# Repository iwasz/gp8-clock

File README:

Stopwatch project for moto-gymkhana.
In case you don't know what is moto-gymkhana : https://www.youtube.com/watch?v=KFEh59GVMnQ

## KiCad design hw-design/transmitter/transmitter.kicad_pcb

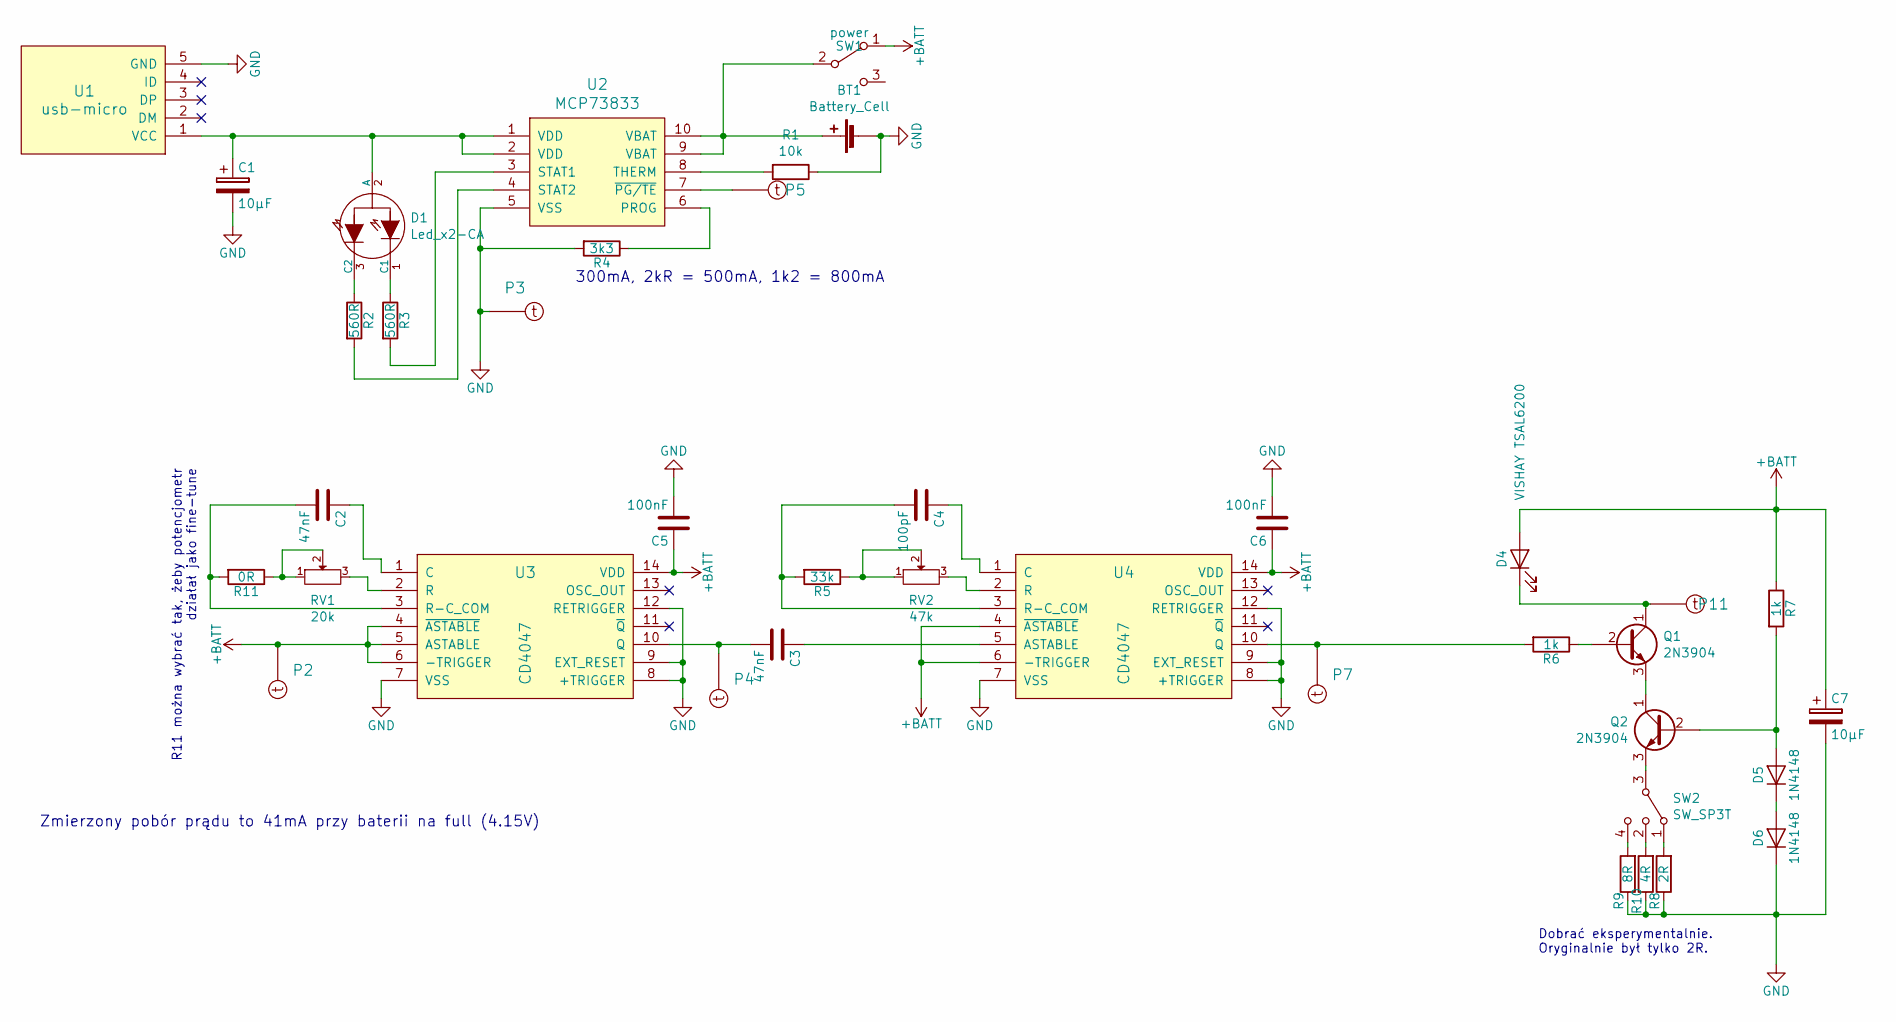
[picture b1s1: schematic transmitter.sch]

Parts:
BT1: Battery_Cell; BatteryHolder_MPD_BH-18650-PC2
C1, C7: 10µF; c_tant_B-pins21
C2, C3: 47nF; C_0603_1608Metric
C4: 100pF; C_0603_1608Metric
C5, C6: 100nF; C_0603_1608Metric
D1: Led_x2-CA; led_3mm-3pins
D4: VISHAY TSAL6200; LED_D5.0mm_Horizontal_O3.81mm_Z3.0mm
D5, D6: 1N4148; D_SOD-323
P2, P3, P4, P5, P7, P11: test-double; testpad-2p
Q1, Q2: 2N3904; TO-92
R1: 10k; R_0603_1608Metric
R2, R3: 560R; R_0603_1608Metric
R4: 3k3; R_0603_1608Metric
R5: 33k; R_0603_1608Metric
R6, R7: 1k; R_0603_1608Metric
R8: 2R; R_0805_2012Metric
R9: 8R; R_0805_2012Metric
R10: 4R; R_0805_2012Metric
R11: 0R; R_0603_1608Metric
RV1: 20k; Potentiometer_Bourns_3296W_Vertical
RV2: 47k; Potentiometer_Bourns_3296W_Vertical
SW1: power; MFP 201 NR
SW2: SW_SP3T; MFP-1323-R
U1: usb-micro; conn_usb_B_micro_smd-2-nohole
U2: MCP73833; MSOP-10_3x3mm_P0.5mm
U3, U4: CD4047; SOIC-14_3.9x8.7mm_P1.27mm

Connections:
+BATT: C5.1, C6.1, C7.1, D4.2 (A), P2.1, R7.1, SW1.1 (A), U3.4 (~ASTABLE), U3.5 (ASTABLE), U3.6 (-TRIGGER), U3.14 (VDD), U4.4 (~ASTABLE), U4.6 (-TRIGGER), U4.14 (VDD)
GND: BT1.2 (-), C1.2, C5.2, C6.2, C7.2, D6.1 (K), P3.1, R1.1, R4.2, R8.1, R9.1, R10.1, U1.5 (GND), U2.5 (VSS), U3.7 (VSS), U3.8 (+TRIGGER), U3.9 (EXT_RESET), U3.12 (RETRIGGER), U4.7 (VSS), U4.8 (+TRIGGER), U4.9 (EXT_RESET), U4.12 (RETRIGGER)
unnamed: BT1.1 (+), SW1.2 (B), U2.9 (VBAT), U2.10 (VBAT)
unnamed: C1.1, D1.2 (A), U1.1 (VCC), U2.1 (VDD), U2.2 (VDD)
unnamed: C2.1, U3.1 (C)
unnamed: C2.2, R11.2, U3.3 (R-C_COM)
unnamed: C3.1, U4.5 (ASTABLE)
unnamed: C3.2, P4.1, U3.10 (Q)
unnamed: C4.1, U4.1 (C)
unnamed: C4.2, R5.2, U4.3 (R-C_COM)
unnamed: D1.1 (C1), R3.1
unnamed: D1.3 (C2), R2.1
unnamed: D4.1 (K), P11.1, Q1.1 (C)
unnamed: D5.1 (K), D6.2 (A)
unnamed: D5.2 (A), Q2.2 (B), R7.2
unnamed: P5.1, U2.7 (~PG/TE)
unnamed: P7.1, R6.2, U4.10 (Q)
unnamed: Q1.2 (B), R6.1
unnamed: Q1.3 (E), Q2.1 (C)
unnamed: Q2.3 (E), SW2.3
unnamed: R1.2, U2.8 (THERM)
unnamed: R2.2, U2.4 (STAT2)
unnamed: R3.2, U2.3 (STAT1)
unnamed: R4.1, U2.6 (PROG)
unnamed: R5.1, RV2.1, RV2.2
unnamed: R8.2, SW2.1
unnamed: R9.2, SW2.4
unnamed: R10.2, SW2.2
unnamed: R11.1, RV1.1, RV1.2
unnamed: RV1.3, U3.2 (R)
unnamed: RV2.3, U4.2 (R)

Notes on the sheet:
300mA, 2kR = 500mA, 1k2 = 800mA
Zmierzony pobór prądu to 41mA przy baterii na full (4.15V)
Dobrać eksperymentalnie. Oryginalnie był tylko 2R.
R11 można wybrać tak, żeby potencjometr działał jako fine-tune

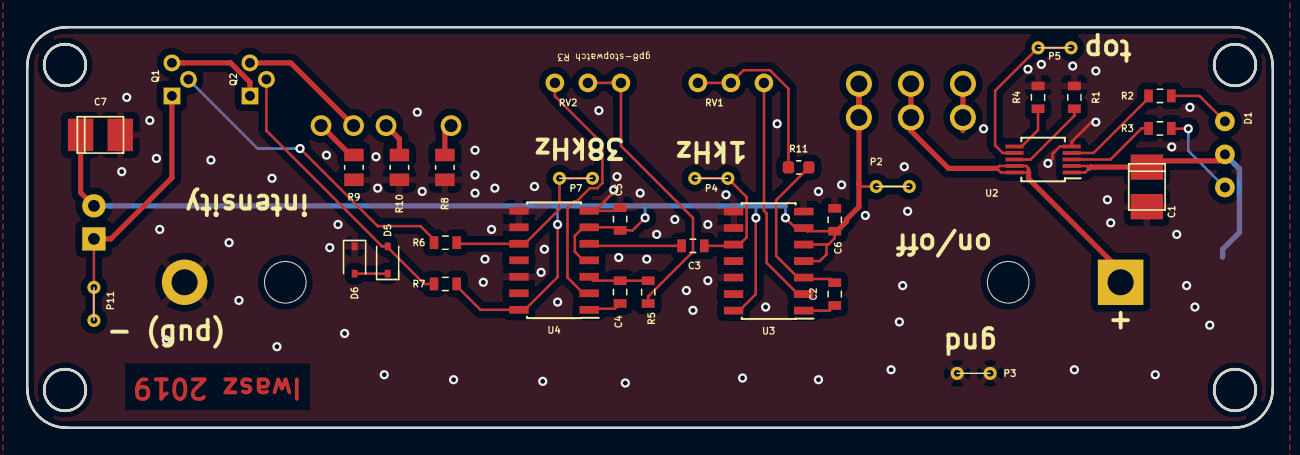
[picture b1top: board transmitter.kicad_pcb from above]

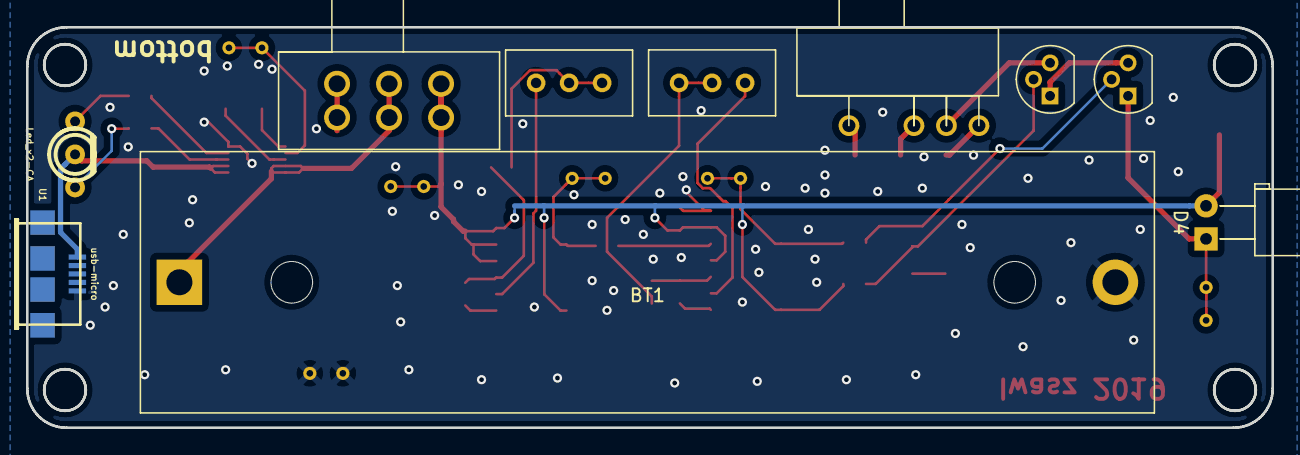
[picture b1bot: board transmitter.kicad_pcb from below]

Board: 2 copper layers, 95.8 x 30.8 mm, 39 parts (10 on the bottom side), 31 nets.

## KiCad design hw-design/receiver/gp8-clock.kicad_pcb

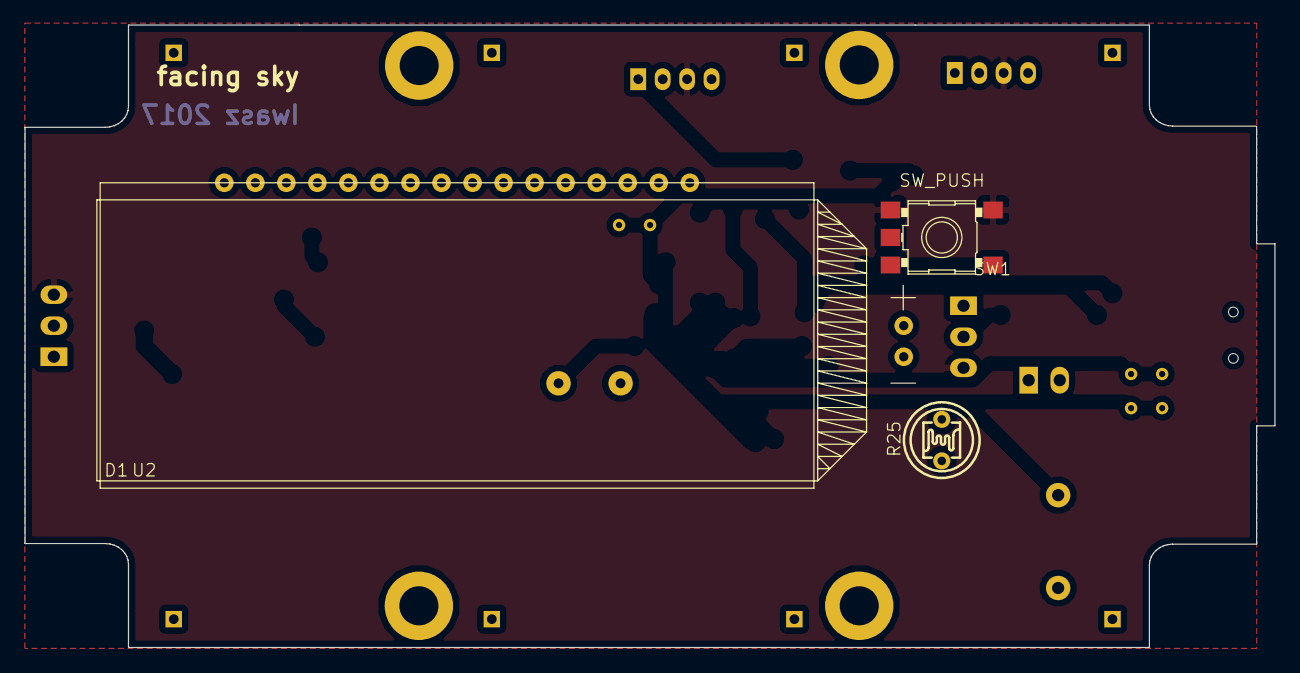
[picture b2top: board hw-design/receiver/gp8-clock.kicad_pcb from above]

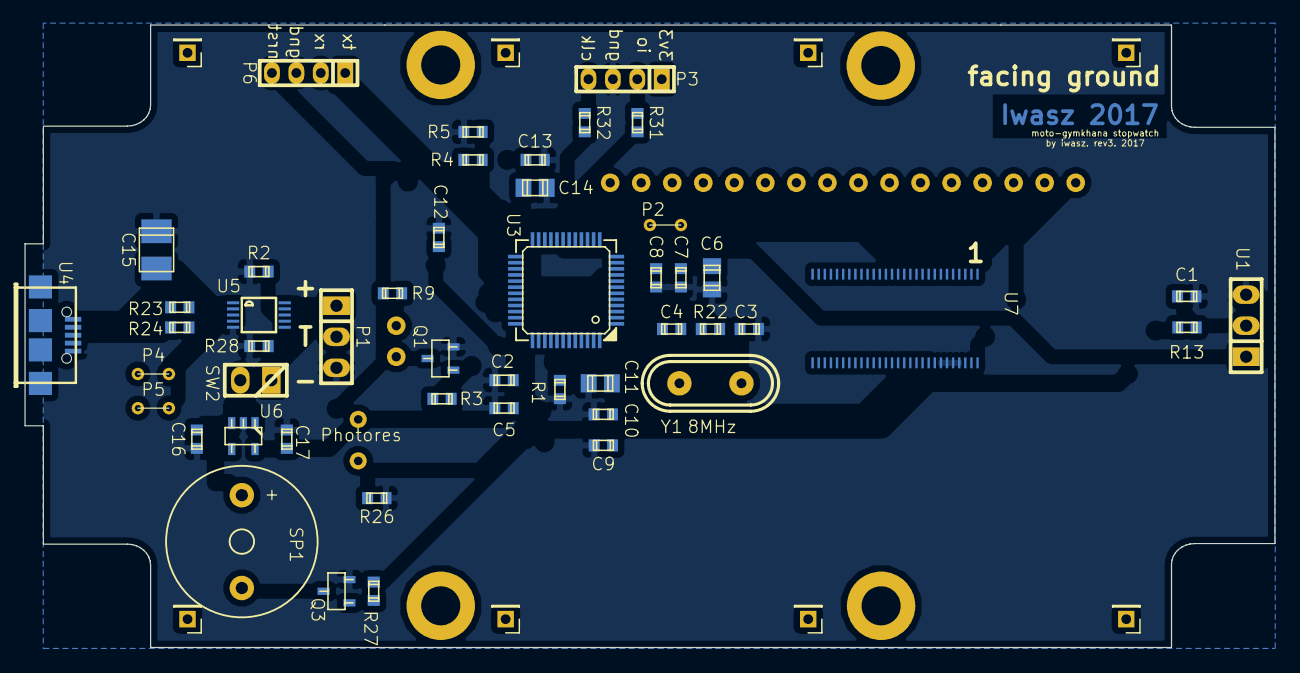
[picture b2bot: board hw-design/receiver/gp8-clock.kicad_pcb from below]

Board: 2 copper layers, 102.3 x 50.9 mm, 65 parts (61 on the bottom side), 54 nets, no tracks yet.

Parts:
C1: C; c_0603
C2: 1µF; c_0603
C3, C4: ?10pF; c_0603
C5: 10nF; c_0603
C6, C11, C14: 4.7µF; c_0805
C7, C8, C9, C10, C12, C13: 100nF; c_0603
C15: 10µF; c_tant_B
C16, C17: 1µF, X5R, X7R, 25V; c_0603
D1: LED; weight-scale-backlight
J1, J10, J11, J12: CONN_01X01; MountingHole_3.2mm_M3_DIN965_Pad
J2, J3, J4, J5, J6, J7, J8, J9: CONN_01X01; Pin_Header_Straight_1x01_Pitch2.00mm
P1: CONN_01X03; pin_strip_3
P2, P4, P5: test-double; testpad-2p
P3, P6: CONN_01X04; pin_strip_2mm_4
Q1, Q3: BC847; sot23
R1, R2, R26: 10k; r_0603
R3, R27: 1k; r_0603
R4, R5: 5k6; r_0603
R9: 560R; r_0603
R13: 1R; r_0603
R22: 220R; r_0603
R23, R24, R31, R32: 22R; r_0603
R25: Photores; T0-46-A10XX
R28: 3k3; r_0603
SP1: BUZZER; Buzzer_12x9.5RM7.6
SW1: SW_PUSH; tact-switch-smd
SW2: power; pin_strip_2
U1: TSOP39538; pin_strip_3
U2: weight-scale-lcd
U3: STM32F072CB / STM32F042C6; lqfp48
U4: usb-micro; conn_usb_B_micro_smd-2
U5: MCP73833; MSOP10
U6: MIC5504; sot23-5
U7: PCF85176T; TSSOP56-6
Y1: 8MHz; crystal_hc-49s

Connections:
+3V3: C2.1, C5.1, C6.1, C7.1, C8.1, C9.1, C10.1, C11.1, C13.1, C14.1, C17.1, P3.1, R13.1, R25.1, U3.9, U3.24, U3.36, U3.48, U6.5, U7.48, U7.55
+5V: C15.1, U4.1, U5.1, U5.2
+BATT: C16.1, R4.2, R9.2, SP1.1, SW2.2, U6.1, U6.3
/Sheet56372EC5/complete: P5.1, U3.2, U5.4
/Sheet56372EC5/progress: P4.1, U3.46, U5.3
/backlight: R3.1, U3.11
/consoleRx: P6.2, U3.31
/consoleTx: P6.1, U3.30
/ir: U1.1, U3.19
/nrst: P2.1, P6.4, U3.7
/screen/scl: U3.42, U7.45
/screen/sda: U3.43, U7.44
/sense: R4.1, R5.2, U3.13
/sound: R27.1, U3.4
/swdclk: R32.2, U3.37
/swdio: R31.2, U3.34
GND: C1.2, C2.2, C3.2, C4.2, C5.2, C6.2, C7.2, C8.2, C9.2, C10.2, C11.2, C12.2, C13.2, C14.2, C15.2, C16.2, C17.2, P1.3, P3.3, P6.3, Q1.3, Q3.3, R1.2, R2.1, R5.1, R26.2, R28.2, SW1.2, U1.3, U3.8, U3.23, U3.35, U3.47, U4.5, U5.5, U6.2, U7.49, U7.50, U7.51, U7.52, U7.53, U7.54
unnamed: C1.1, R13.2, U1.2
unnamed: C3.1, U3.5, Y1.1
unnamed: C4.1, R22.2, Y1.2
unnamed: C12.1, SW1.1, U3.45
unnamed: D1.1, Q1.2
unnamed: D1.2, R9.1
unnamed: P1.1, SW2.1, U5.9, U5.10
unnamed: P1.2, R2.2, U5.8
unnamed: P3.2, R31.1
unnamed: P3.4, R32.1
unnamed: Q1.1, R3.2
unnamed: Q3.1, R27.2
unnamed: Q3.2, SP1.2
unnamed: R1.1, U3.44
unnamed: R22.1, U3.6
unnamed: R23.1, U4.2
unnamed: R23.2, U3.32
unnamed: R24.1, U4.3
unnamed: R24.2, U3.33
unnamed: R25.2, R26.1, U3.3
unnamed: R28.1, U5.6
unnamed: U2.1, U7.56
unnamed: U2.2, U7.2
unnamed: U2.3, U7.1
unnamed: U2.4, U7.3
unnamed: U2.5, U7.4
unnamed: U2.6, U7.5
unnamed: U2.7, U7.6
unnamed: U2.8, U7.7
unnamed: U2.9, U7.8
unnamed: U2.10, U7.9
unnamed: U2.11, U7.10
unnamed: U2.12, U7.11
unnamed: U2.13, U7.12
unnamed: U2.14, U7.13
unnamed: U2.15, U7.14
unnamed: U2.16, U7.15

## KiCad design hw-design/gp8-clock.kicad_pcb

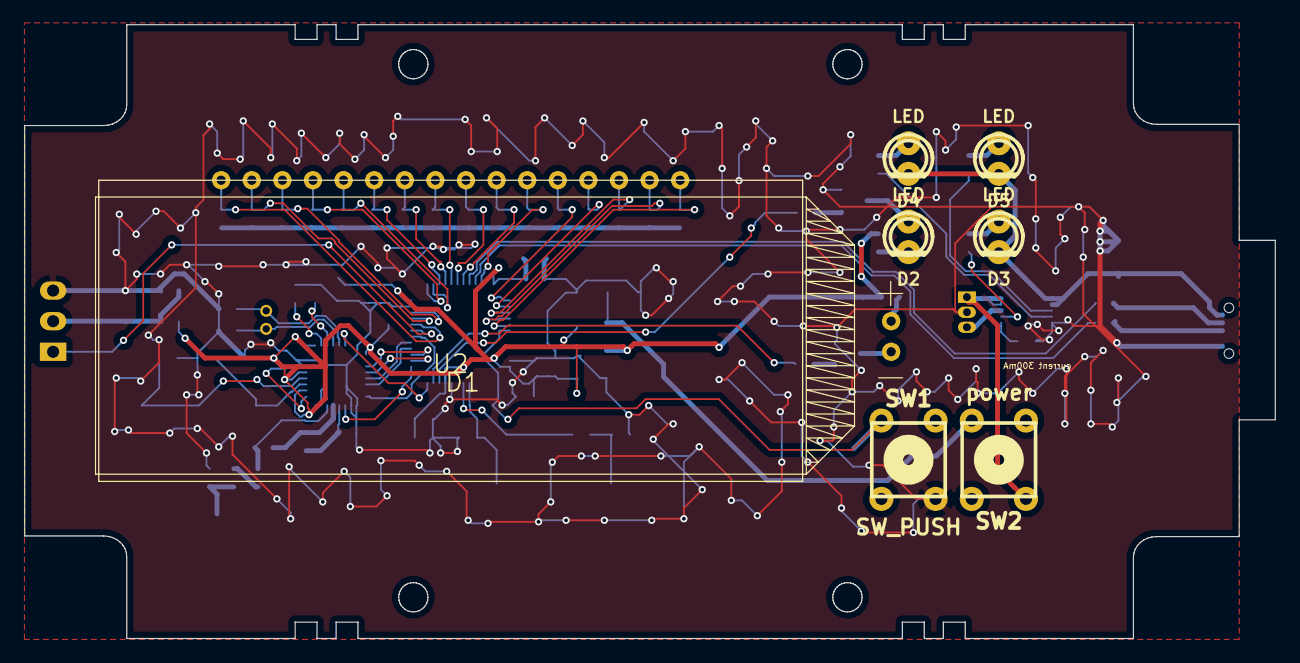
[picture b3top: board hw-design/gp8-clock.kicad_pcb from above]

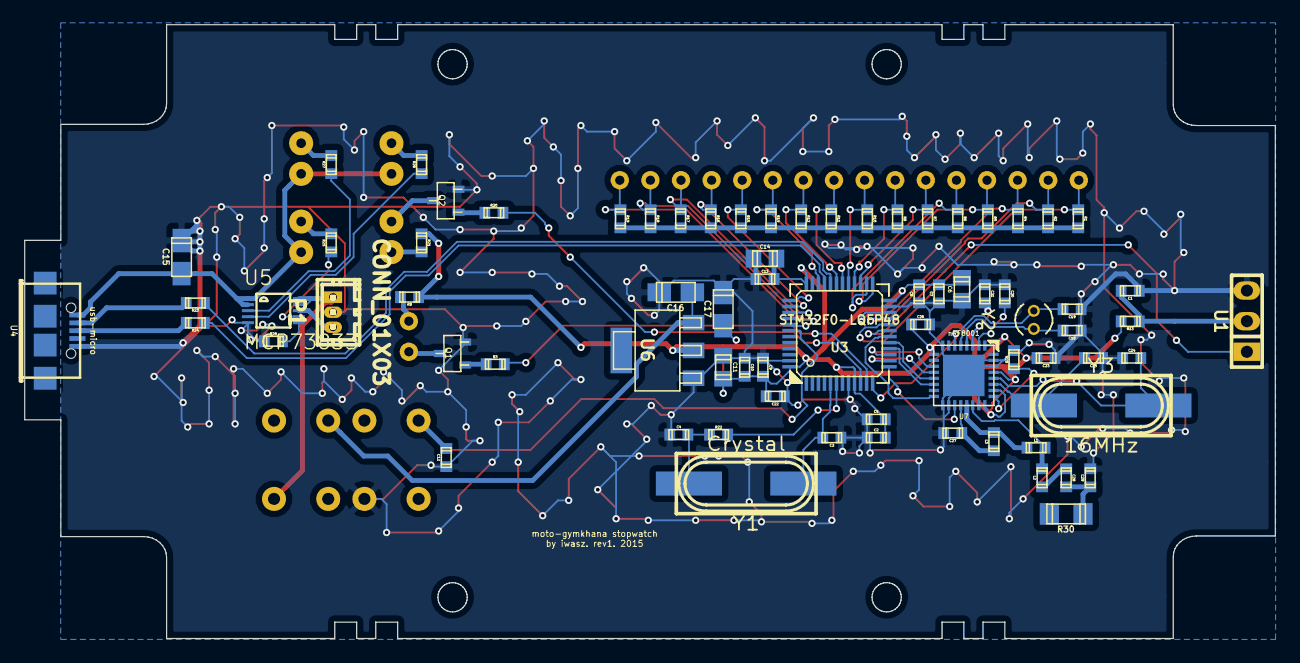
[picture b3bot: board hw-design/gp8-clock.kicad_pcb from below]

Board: 2 copper layers, 103.8 x 50.9 mm, 82 parts (74 on the bottom side), 67 nets.

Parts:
C1: C; c_0603
C2: 1µF; c_0603
C3, C4: ?10pF; c_0603
C5: 10nF; c_0603
C6, C11, C14: 4.7µF; c_0805
C7, C8, C9, C10, C12, C13, C20, C22, C23: 100nF; c_0603
C15, C16, C17: 10µF; c_tant_A
C18, C19: 15pF; c_0603
C21: 33nF; c_0603
C24, C25: 10pF; c_0603
C26: 1nF; c_0603
C27: 2.2nF; c_0603
C28: 1.8pF; c_0603
C29: 1.2pF; c_0603
D1: LED; weight-scale-backlight
D2, D5: LED; led_3mm_red
D3: LED; led_3mm_yellow
D4: LED; led_3mm_green
L1: 8.2nH; r_0603
L2: 3.9nH; r_0603
L3: 5.6nH; r_0603
P1: CONN_01X03; df13-3p-125dsa
Q1, Q2: Q_NPN_BCE; sot23
R1, R2, R4, R5, R6, R7, R8, R10, R11, R12, R14, R15, R16, R17, R18, R19: 33k; r_0603
R3, R20: 1k; r_0603
R9, R21, R25, R26, R27: 560R; r_0603
R13: 100R; r_0603
R22: R; r_0603
R23, R24: 22R; r_0603
R28: 3k3; r_0603
R29: 22k; r_0603
R30: AMCA31; r_1206
SW1: SW_PUSH; PCB_PUSH
SW2: power; PCB_PUSH
U1: TSOP39538; pin_strip_3
U2: weight-scale-lcd
U3: STM32F0-LQFP48; lqfp48
U4: usb-micro; conn_usb_B_micro_smd-2
U5: MCP73833; MSOP10
U6: AP1117D33; sot223
U7: nRF8001; pvqfn-n32
Y1: Crystal; hc-49_smd
Y2: 32kHz; Crystal_Round_Vertical_3mm
Y3: 16MHz; hc-49_smd

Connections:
+3V3: C2.1, C5.1, C6.1, C7.1, C8.1, C9.1, C10.1, C11.1, C13.1, C14.1, C17.1, C22.1, C23.1, C26.2, R9.2, R13.1, R21.2, U3.9, U3.24, U3.36, U3.48, U6.2, U7.1, U7.9, U7.24, U7.26, U7.29
+5V: C15.1, D3.2, D4.2, D5.2, U4.1, U5.1, U5.2
+BATT: R1.1, R2.1, R4.1, R5.1, R6.1, R7.1, R8.1, R10.1, R11.1, R12.1, R14.1, R15.1, R16.1, R17.1, R18.1, R19.1
/backlight: R3.1, U3.11
/com1: R1.2, U2.1, U3.20
/com2: R2.2, U2.2, U3.21
/com3: R4.2, U2.3, U3.22
/com4: R5.2, U2.4, U3.25
/indicator: R20.1, U3.10
/ir: U1.1, U3.19
/seg1: R6.2, U2.5, U3.26
/seg2: R7.2, U2.6, U3.27
/seg3: R8.2, U2.7, U3.28
/seg4: R10.2, U2.8, U3.29
/seg5: R11.2, U2.9, U3.30
/seg6: R12.2, U2.10, U3.31
/seg7: R14.2, U2.11, U3.34
/seg8: R15.2, U2.12, U3.37
/seg9: R16.2, U2.13, U3.38
/seg10: R17.2, U2.14, U3.39
/seg11: R18.2, U2.15, U3.40
/seg12: R19.2, U2.16, U3.41
GND: C1.2, C2.2, C3.2, C4.2, C5.2, C6.2, C7.2, C8.2, C9.2, C10.2, C11.2, C12.2, C13.2, C14.2, C15.2, C16.2, C17.2, C18.2, C19.2, C20.2, C21.2, C22.2, C23.2, C24.2, C25.2, C26.1, C27.1, C29.1, P1.2, Q1.3, Q2.3, R28.2, R29.1, SW1.2, U1.3, U3.8, U3.23, U3.47, U4.5, U5.5, U6.1, U7.8, U7.17, U7.18, U7.23, U7.30, U7.31, U7.33
unnamed: C1.1, R13.2, U1.2
unnamed: C3.1, U3.5, Y1.1
unnamed: C4.1, R22.2, Y1.2
unnamed: C12.1, SW1.1, U3.42
unnamed: C16.1, SW2.2, U6.3
unnamed: C18.1, U7.4, Y2.1
unnamed: C19.1, U7.5, Y2.2
unnamed: C20.1, U7.2
unnamed: C21.1, U7.3
unnamed: C24.1, U7.28, Y3.2
unnamed: C25.1, U7.27, Y3.1
unnamed: C27.2, L3.2, U7.20
unnamed: C28.1, C29.2, R30.2
unnamed: C28.2, L2.2
unnamed: D1.1, Q1.2
unnamed: D1.2, R9.1
unnamed: D2.1, Q2.2
unnamed: D2.2, R21.1
unnamed: D3.1, R25.1
unnamed: D4.1, R26.1
unnamed: D5.1, R27.1
unnamed: L1.1, L2.1, U7.22
unnamed: L1.2, L3.1, U7.21
unnamed: P1.1, SW2.1, U5.9, U5.10
unnamed: P1.3, U5.8
unnamed: Q1.1, R3.2
unnamed: Q2.1, R20.2
unnamed: R22.1, U3.6
unnamed: R23.1, U4.2
unnamed: R23.2, U3.32
unnamed: R24.1, U4.3
unnamed: R24.2, U3.33
unnamed: R25.2, U5.7
unnamed: R26.2, U5.4
unnamed: R27.2, U5.3
unnamed: R28.1, U5.6
unnamed: R29.2, U7.25
ble_active: U3.12, U7.6
ble_miso: U3.16, U7.14
ble_mosi: U3.17, U7.13
ble_rdyn: U3.18, U7.16
ble_reqn: U3.14, U7.12
ble_reset: U3.13, U7.19
ble_sck: U3.15, U7.11

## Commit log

2015-08-21 Initial
2015-08-21 7 segment
2015-08-23 Counts up, looks ok
2015-08-31 Counts
2015-09-01 Proponowane ustawienia timera
2015-09-02 OC config
2015-09-02 Usunięty komentgarz
2015-09-03 Code formatting using clang_format
2015-09-05 Works on F4
2015-09-06 Works on the target device
2015-09-07 Works on the target configuration. First tests on attery power. Looks promising, 5m (15ft) range. Both draws 50mA
2015-11-06 hw design kicad
2015-11-10 Powiększona płytka
2015-11-10 Documentation, directory split, minors
2015-11-11 Skończona rewizja r1, wysłane do satlanfd
2016-01-03 Revision 2
2016-01-07 Rewizja 2
2016-01-27 Funkcjonaloność tego zegara na LEDac jest w tym momencie powtórzona na LCDku
2016-01-27 Pipczenie
2016-02-18 Poprawki
2016-02-23 Jakieś próby polepszenia jakości obrazu
2016-09-14 Testy z tym fajnym chipem od LCD driverem
2017-03-06 HW changes, removed BLE, and changed chanrging and ldo circuits
2017-03-06 2017 improvements
2017-05-15 New hw&fw
2017-05-15 Gerbers added
2017-05-16 Timer runs, display is refreshed, stopwatch works, but cannot be stopped
2017-05-16 Pre refactoring functionality restored
2017-05-16 Separate files created (each for each class)
2017-05-17 Stopwatch more intuitive nosw. State machine improved.
2017-05-17 Beam detection, and indication on the LCD
2017-05-17 Clock finally set to hardware
2017-05-17 Buzzer
2017-05-17 Debug, ADC
2017-05-23 Backlight and battery monotoring. Faulty start/stop mehcanism
2017-05-24 New way of telling if beam is present or not
2017-05-24 State machine (starting and stopping) improved
2017-05-24 I finally managed to hack ADC that it works with 2 channels in pollingmode
2017-05-24 ADC works, battery and ambient light are measured correctly
2017-05-24 Refactored : classes moved to separate files
2017-05-24 History and hiscroe in memory
2017-05-24 Best time signals
2017-06-22 Hiscore saving finally seems to be working!
2017-06-22 History is saved now
2017-06-29 Button
2017-06-29 Hiscore and histroy clearing options in user interface
2017-06-29 Clearing UI options improved
2017-09-07 USB work in progress. Enumerates OK
2017-09-07 USB work in progress. Prints "." dots in serial console
2017-09-08 Fixed USB connectivity. Memory allocation functions were undefined, so silently no allocation was performed in one spot in the code.
2017-09-08 Results are reported via USB, but there are some bugs
2017-09-08 Time printouts now padded with zeroes
2017-09-08 Fixed buffer overflow
2017-09-08 Better history display
2017-11-04 Jakieś zamiany dostosowujące do najnowszej wersji libmicro
2017-11-04 Zapomniane pliki
2018-02-14 Somoe old fixes
2019-07-03 Many changes
2019-07-06 New version of the transmitter and its enclosure is done
